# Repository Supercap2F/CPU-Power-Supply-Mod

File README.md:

# CPU Power Supply Mod
Project description can be found here: http://www.electronicspoint.com/projectlogs/cpu-power-supply-mod.74/

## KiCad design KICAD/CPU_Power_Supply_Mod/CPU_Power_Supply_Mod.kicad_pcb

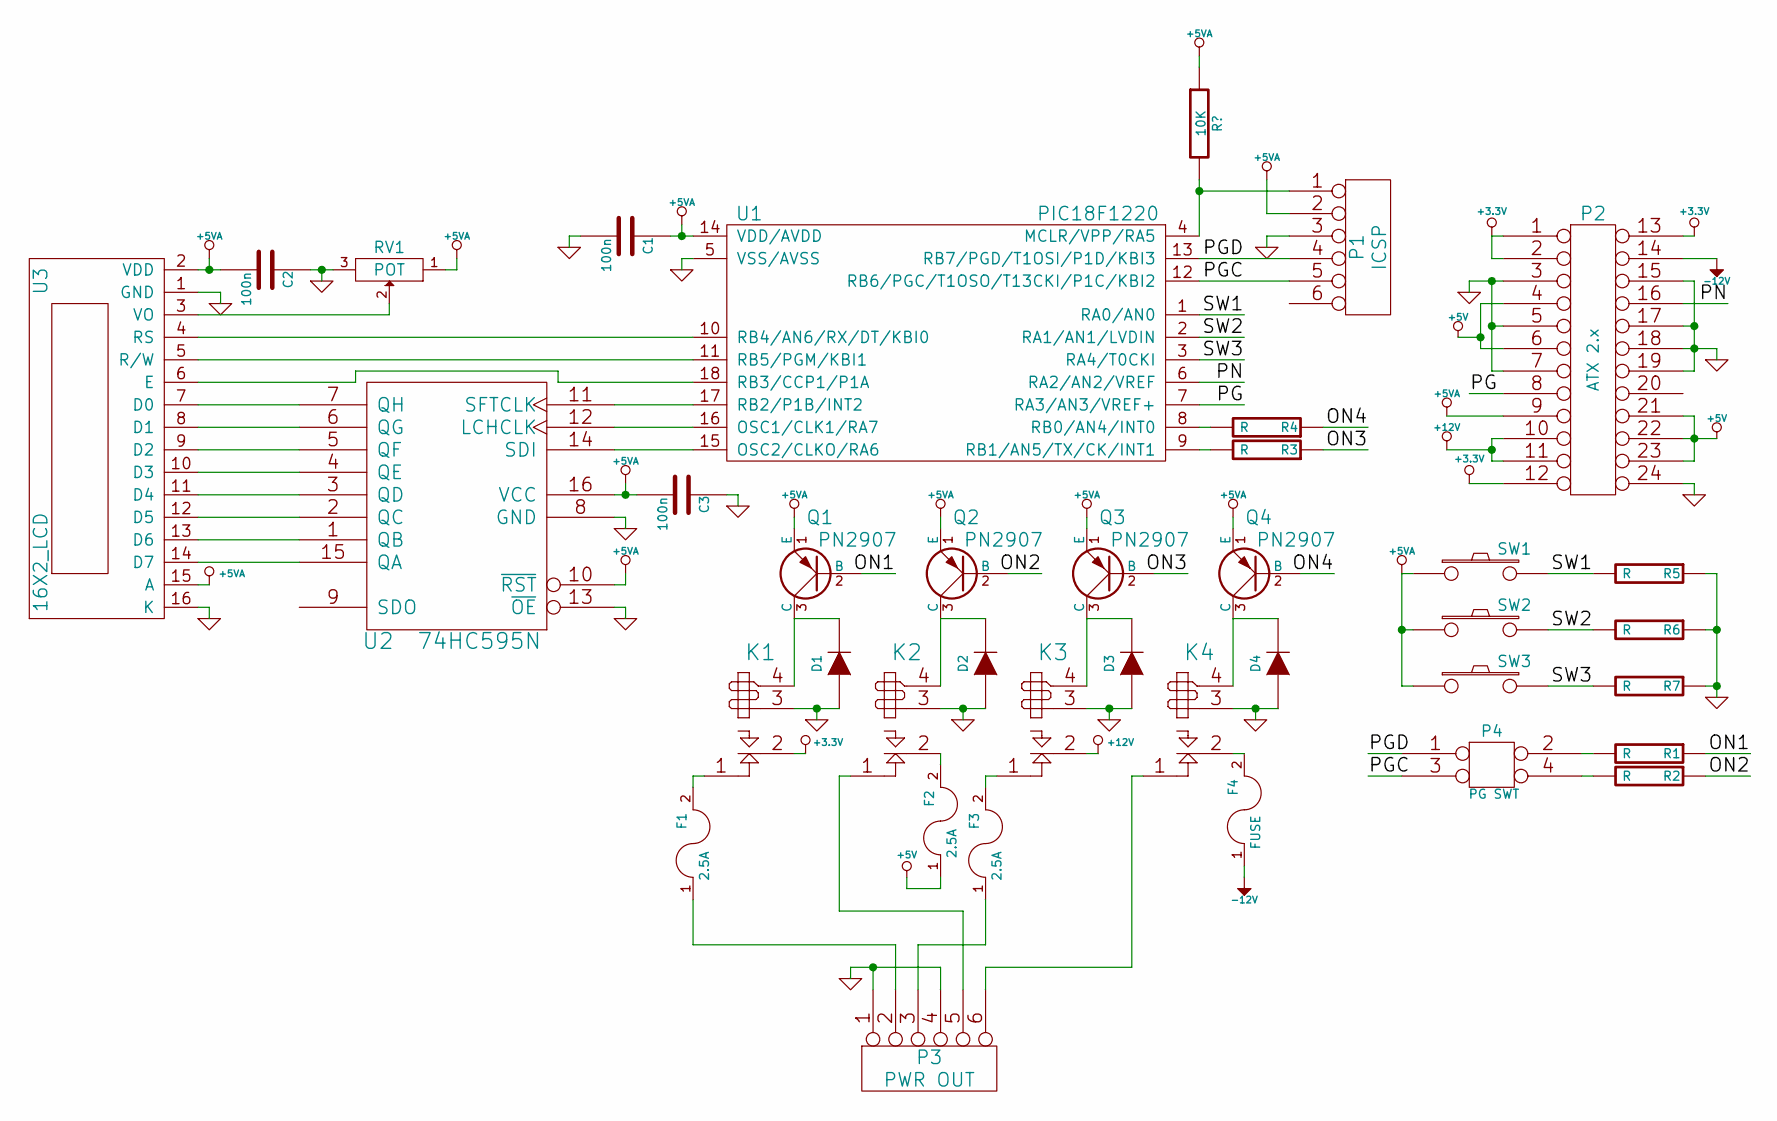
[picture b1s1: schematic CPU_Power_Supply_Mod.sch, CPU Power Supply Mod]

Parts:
C1, C2, C3: 100n
D1, D2, D3, D4: DIODE
F1, F2, F3: 2.5A
F4: FUSE
K1, K2, K3, K4: RELAY_SPST
P1: ICSP
P2: ATX 2.x
P3: PWR OUT
P4: PG SWT
Q1, Q2, Q3, Q4: PN2907
R1, R2, R3, R4, R5, R6, R7: R
RV1: POT
SW1, SW2, SW3: SW_PUSH
U1: PIC18F1220
U2: 74HC595N
U3: 16X2_LCD

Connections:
+3.3V: K1.2 (C2), P2.1, P2.2, P2.12 (P23), P2.13
+5V: F2.1, P2.4, P2.6, P2.21, P2.22, P2.23
+5VA: C1.1, C2.2, C3.2, P1.2, P2.9, Q1.1 (E), Q2.1 (E), Q3.1 (E), Q4.1 (E), RV1.1, SW1.1, SW2.1, SW3.1, U1.14 (VDD/AVDD), U2.10 (~RST), U2.16 (VCC), U3.2 (VDD), U3.15 (A)
+12V: K3.2 (C2), P2.10, P2.11 (P12)
-12V: F4.1, P2.14
/ON1: Q1.2 (B), R1.1
/ON2: Q2.2 (B), R2.1
/ON3: Q3.2 (B), R3.1
/ON4: Q4.2 (B), R4.1
/PG: P2.8, U1.7 (RA3/AN3/VREF+)
/PGC: P1.5, P4.3, U1.12 (RB6/PGC/T1OSO/T13CKI/P1C/KBI2)
/PGD: P1.4, P4.1, U1.13 (RB7/PGD/T1OSI/P1D/KBI3)
/PN: P2.16, U1.6 (RA2/AN2/VREF)
/SW1: R5.2, SW1.2, U1.1 (RA0/AN0)
/SW2: R6.2, SW2.2, U1.2 (RA1/AN1/LVDIN)
/SW3: R7.2, SW3.2, U1.3 (RA4/T0CKI)
GND: C1.2, C2.1, C3.1, D1.1 (A), D2.1 (A), D3.1 (A), D4.1 (A), K1.3, K2.3, K3.3, K4.3, P1.3, P2.3, P2.5, P2.7, P2.15, P2.17, P2.18, P2.19, P2.24, P3.1, P3.4, R5.1, R6.1, R7.1, RV1.3, U1.5 (VSS/AVSS), U2.8 (GND), U2.13 (~OE), U3.1 (GND), U3.16 (K)
unnamed: P1.1, U1.4 (MCLR/VPP/RA5)
unnamed: RV1.2, U3.3 (VO)
unnamed: U2.15 (QA), U3.14 (D7)
unnamed: U2.1 (QB), U3.13 (D6)
unnamed: U2.2 (QC), U3.12 (D5)
unnamed: U2.3 (QD), U3.11 (D4)
unnamed: U2.4 (QE), U3.10 (D3)
unnamed: U2.5 (QF), U3.9 (D2)
unnamed: U2.6 (QG), U3.8 (D1)
unnamed: U2.7 (QH), U3.7 (D0)
unnamed: U1.15 (OSC2/CLKO/RA6), U2.14 (SDI)
unnamed: U1.18 (RB3/CCP1/P1A), U3.6 (E)
unnamed: U1.10 (RB4/AN6/RX/DT/KBI0), U3.4 (RS)
unnamed: U1.11 (RB5/PGM/KBI1), U3.5 (R/W)
unnamed: U1.16 (OSC1/CLK1/RA7), U2.12 (LCHCLK)
unnamed: U1.17 (RB2/P1B/INT2), U2.11 (SFTCLK)
unnamed: F3.1, P3.3
unnamed: F2.2, K2.2 (C2)
unnamed: P4.4, R2.2
unnamed: P4.2, R1.2
unnamed: D4.2 (K), K4.4, Q4.3 (C)
unnamed: D3.2 (K), K3.4, Q3.3 (C)
unnamed: D2.2 (K), K2.4, Q2.3 (C)
unnamed: D1.2 (K), K1.4, Q1.3 (C)
unnamed: R4.2, U1.8 (RB0/AN4/INT0)
unnamed: R3.2, U1.9 (RB1/AN5/TX/CK/INT1)
unnamed: F1.1, P3.2
unnamed: F1.2, K1.1 (R1)
unnamed: K2.1 (R1), P3.5
unnamed: F3.2, K3.1 (R1)
unnamed: K4.1 (R1), P3.6
unnamed: F4.2, K4.2 (C2)

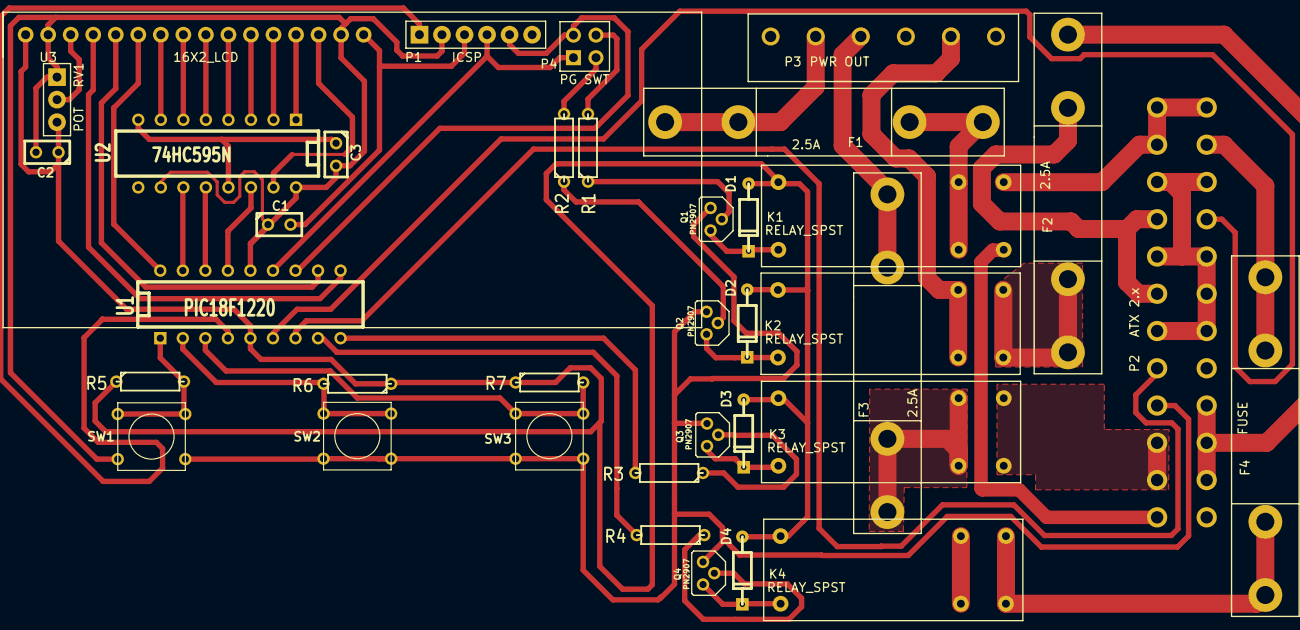
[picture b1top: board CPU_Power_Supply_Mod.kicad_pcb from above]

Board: 2 copper layers, 37 parts (0 on the bottom side), 49 nets.

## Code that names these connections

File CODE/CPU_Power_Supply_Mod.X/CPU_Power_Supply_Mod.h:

/***********************************************
 * File:   CPU_Power_Supply_Mod.h              *
 * Author: Supercap2F                          *
 *                                             *
 * Created on October 24, 2015, 4:24 PM        *
 ***********************************************/
#ifndef CPU_POWER_SUPPLY_MOD_H
#define	CPU_POWER_SUPPLY_MOD_H

/***********************************************
 * Definitions                                 *
 ***********************************************/
#define _XTAL_FREQ 0x7A1200 // set system clock to 8MHz

#define SW1 PORTAbits.RA0 
#define SW2 PORTAbits.RA1
#define PN  LATAbits.LATA2 // power on
#define PG  PORTAbits.RA3 // power good 
#define SW3 PORTAbits.RA4

#define RLn12V LATBbits.LATB0
#define RL12V  LATBbits.LATB1
#define RL5V   LATBbits.LATB7
#define RL3V3  LATBbits.LATB6

#define PAIR_ALL 0b00001111

#endif	/* CPU_POWER_SUPPLY_MOD_H */

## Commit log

2015-09-21 Changed Read Me File
2015-09-21 Added Project Files
2015-09-22 Changed README.md File
2015-09-24 Updated PCB
2015-10-15 Added Code
2015-10-26 Updated Code
2015-10-29 Updated Schematic
2015-11-02 Finished most all of the code - Needs a couple tweeks
2015-11-03 Finished Code - Comments need some work though
2015-11-14 Finished Project
